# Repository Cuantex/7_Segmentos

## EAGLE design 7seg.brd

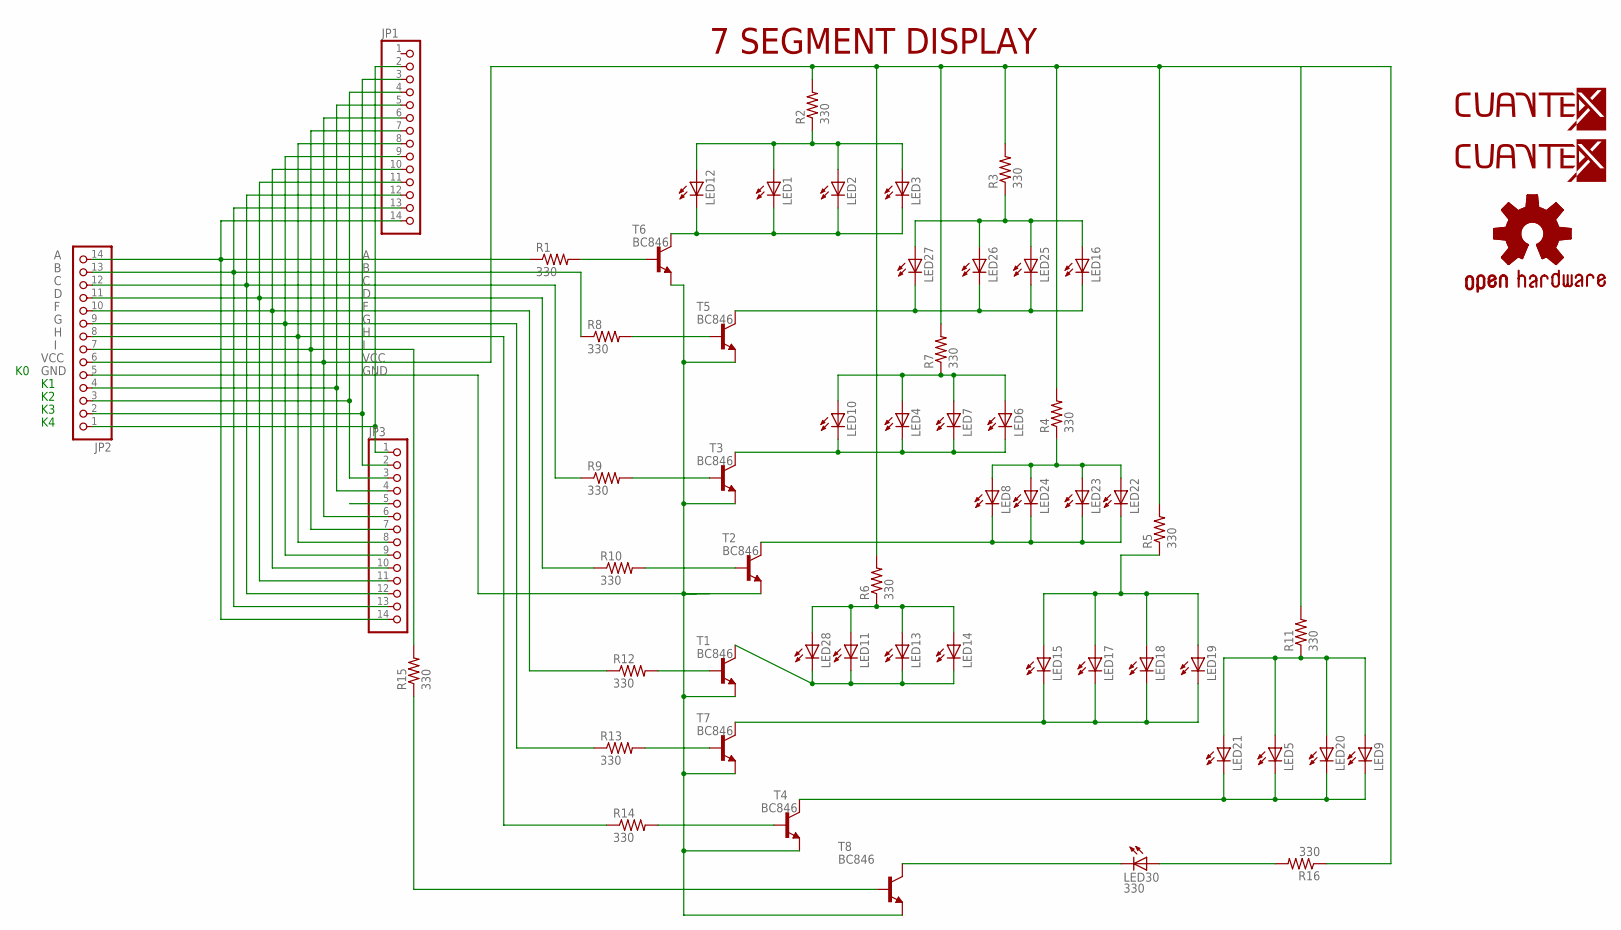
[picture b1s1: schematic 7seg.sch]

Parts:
GOLD_ORB_SM2: OSHWLOGO_GOLD_ORB_MED; OSHW1
JP1, JP2, JP3: PINHD-1X14; 1X14
LED1, LED2, LED3, LED4, LED5, LED6, LED7, LED8, LED9, LED10, LED11, LED12, LED13, LED14, LED15, LED16, LED17, LED18, LED19, LED20, LED21, LED22, LED23, LED24, LED25, LED26, LED27, LED28: LED_E; LED_1206
LED30: 330; LED_1206
R1, R2, R3, R4, R5, R6, R7, R8, R9, R10, R11, R12, R13, R14, R15, R16: 330; R0603
T1, T2, T3, T4, T5, T6, T7, T8: BC846; SOT23
U$1: LOGO-TOP-20MM; C-0
U$2: LOGO-BOT-60MM; B-60

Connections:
A: JP1.14, JP2.14, JP3.14, R1.1
B: JP1.13, JP2.13, JP3.13, R8.1
C: JP1.12, JP2.12, JP3.12, R9.1
D: JP1.11, JP2.11, JP3.11, R10.1
F: JP1.10, JP2.10, JP3.10, R12.1
G: JP1.9, JP2.9, JP3.9, R13.1
GND: JP2.5, JP3.5, T1.2 (E), T2.2 (E), T3.2 (E), T4.2 (E), T5.2 (E), T6.2 (E), T7.2 (E), T8.2 (E)
H: JP1.8, JP2.8, JP3.8, R14.1
I: JP1.7, JP2.7, JP3.7, R15.2
unnamed: LED5.A, LED9.A, LED20.A, LED21.A, R11.1
unnamed: LED8.C, LED22.C, LED23.C, LED24.C, T2.3 (C)
unnamed: LED16.A, LED25.A, LED26.A, LED27.A, R3.1
unnamed: R12.2, T1.1 (B)
unnamed: LED11.C, LED13.C, LED14.C, LED28.C, T1.3 (C)
unnamed: LED15.A, LED17.A, LED18.A, LED19.A, R5.1
unnamed: LED30.A, R16.2
unnamed: LED1.C, LED2.C, LED3.C, LED12.C, T6.3 (C)
unnamed: R1.2, T6.1 (B)
unnamed: R8.2, T5.1 (B)
unnamed: LED16.C, LED25.C, LED26.C, LED27.C, T5.3 (C)
unnamed: R15.1, T8.1 (B)
unnamed: R9.2, T3.1 (B)
unnamed: LED4.C, LED6.C, LED7.C, LED10.C, T3.3 (C)
unnamed: R10.2, T2.1 (B)
unnamed: LED30.C, T8.3 (C)
unnamed: R13.2, T7.1 (B)
unnamed: LED15.C, LED17.C, LED18.C, LED19.C, T7.3 (C)
unnamed: R14.2, T4.1 (B)
unnamed: LED5.C, LED9.C, LED20.C, LED21.C, T4.3 (C)
unnamed: LED1.A, LED2.A, LED3.A, LED12.A, R2.1
unnamed: LED8.A, LED22.A, LED23.A, LED24.A, R4.1
unnamed: LED4.A, LED6.A, LED7.A, LED10.A, R7.1
unnamed: LED11.A, LED13.A, LED14.A, LED28.A, R6.1
unnamed: JP1.5, JP2.4, JP3.4
unnamed: JP1.4, JP2.3, JP3.3
unnamed: JP1.3, JP2.2, JP3.2
unnamed: JP1.2, JP2.1, JP3.1
VCC: JP1.6, JP2.6, JP3.6, R2.2, R3.2, R4.2, R5.2, R6.2, R7.2, R11.2, R16.1

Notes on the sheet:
7 SEGMENT DISPLAY

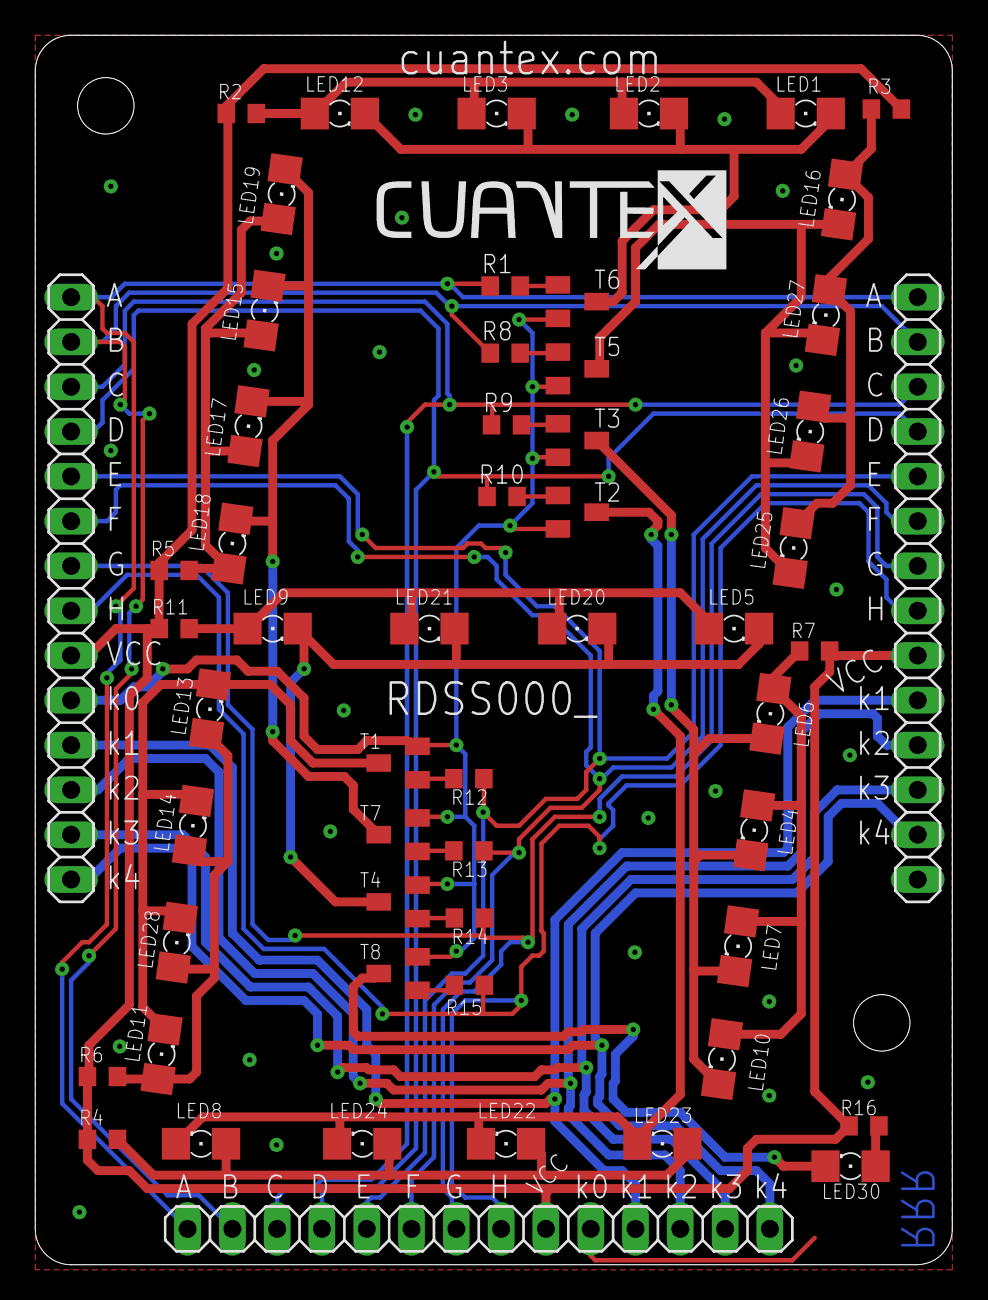
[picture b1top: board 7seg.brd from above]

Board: 2 copper layers, 52.0 x 69.7 mm, 59 parts (1 on the bottom side), 38 nets.

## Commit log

2016-10-18 Archivos en Git
